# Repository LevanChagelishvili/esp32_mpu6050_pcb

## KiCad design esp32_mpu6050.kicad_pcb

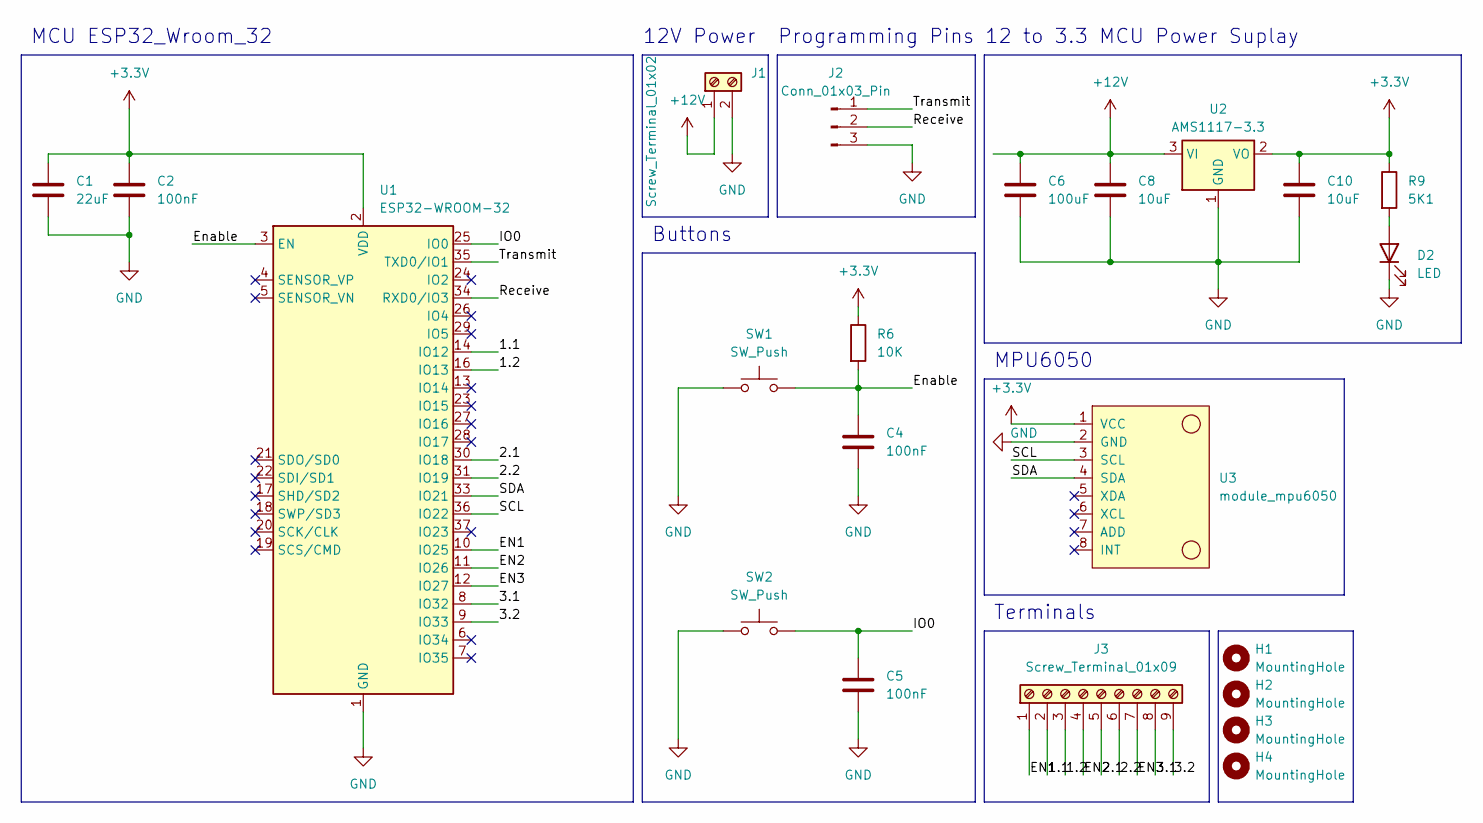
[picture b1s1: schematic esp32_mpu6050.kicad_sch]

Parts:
C1: 22uF; C_0805_2012Metric
C2, C4, C5: 100nF; C_0402_1005Metric
C6: 100uF; C_0805_2012Metric
C8, C10: 10uF; C_0402_1005Metric
D2: LED; LED_0805_2012Metric
H1, H2, H3, H4: MountingHole; MountingHole_3mm_Pad_Via
J1: Screw_Terminal_01x02; TerminalBlock_4Ucon_1x02_P3.50mm_Horizontal
J2: Conn_01x03_Pin; Molex_KK-254_AE-6410-03A_1x03_P2.54mm_Vertical
J3: Screw_Terminal_01x09; TerminalBlock_4Ucon_1x09_P3.50mm_Horizontal
R6: 10K; R_0805_2012Metric
R9: 5K1; R_0805_2012Metric
SW1, SW2: SW_Push; SW_Tactile_SPST_NO_Straight_CK_PTS636Sx25SMTRLFS
U1: ESP32-WROOM-32
U2: AMS1117-3.3; SOT-223-3_TabPin2
U3: module_mpu6050

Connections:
+3.3V: C1.1, C2.1, C10.1, R6.1, R9.1, U1.2 (VDD), U2.2 (VO), U3.1 (VCC)
+12V: C6.1, C8.1, J1.1, U2.3 (VI)
/1.1: J3.2, U1.14 (IO12)
/1.2: J3.3, U1.16 (IO13)
/2.1: J3.5, U1.30 (IO18)
/2.2: J3.6, U1.31 (IO19)
/3.1: J3.8, U1.8 (IO32)
/3.2: J3.9, U1.9 (IO33)
/EN1: J3.1, U1.10 (IO25)
/EN2: J3.4, U1.11 (IO26)
/EN3: J3.7, U1.12 (IO27)
/Enable: C4.1, R6.2, SW1.2, U1.3 (EN)
/IO0: C5.1, SW2.2, U1.25 (IO0)
/Receive: J2.2, U1.34 (RXD0/IO3)
/SCL: U1.36 (IO22), U3.3 (SCL)
/SDA: U1.33 (IO21), U3.4 (SDA)
/Transmit: J2.1, U1.35 (TXD0/IO1)
GND: C1.2, C2.2, C4.2, C5.2, C6.2, C8.2, C10.2, D2.1 (K), J1.2, J2.3, SW1.1, SW2.1, U1.1 (GND), U1.15 (GND), U1.38 (GND), U1.39 (GND), U2.1 (GND), U3.2 (GND)
unnamed: D2.2 (A), R9.2

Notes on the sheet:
Terminals
Buttons
12V Power
Programming Pins
MCU ESP32_Wroom_32
12 to 3.3 MCU Power Suplay
MPU6050

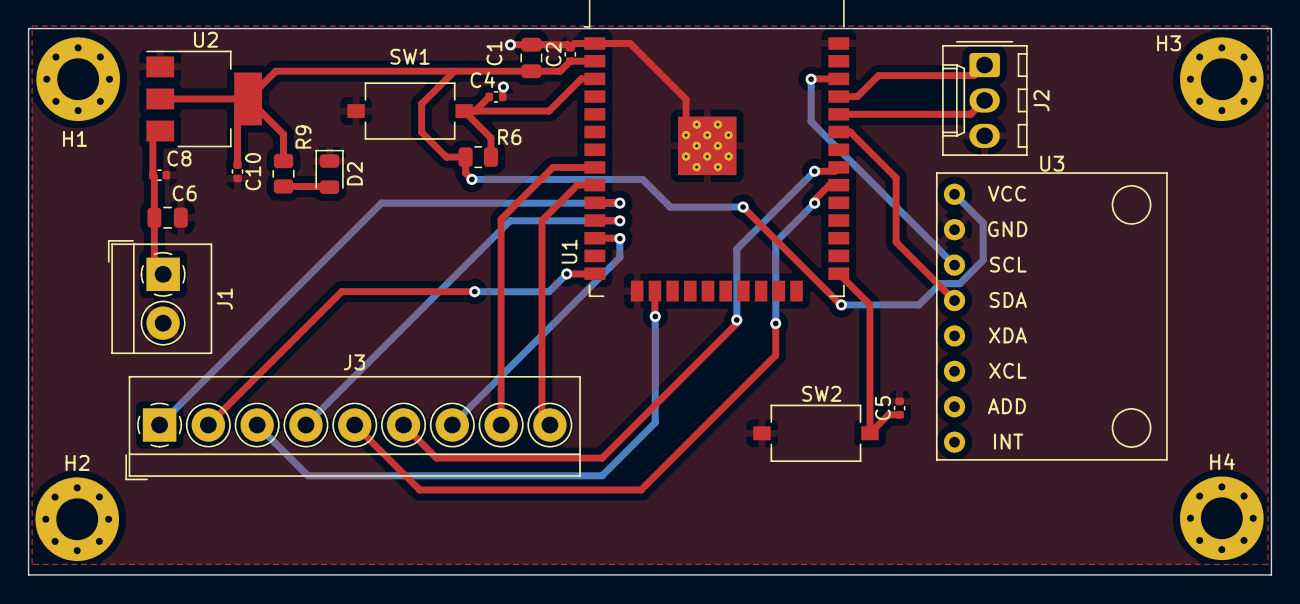
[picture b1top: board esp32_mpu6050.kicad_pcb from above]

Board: 2 copper layers, 89.2 x 39.2 mm, 22 parts (0 on the bottom side), 19 nets.
